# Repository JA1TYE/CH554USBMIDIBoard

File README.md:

# CH554 USB-MIDI Host Board

This board is designed to use [WCH's 8-bit MCU CH554](http://wch-ic.com/products/CH554.html) as a USB-MIDI Host.

Firmware for this board is available on [CH554USBMIDIHost](https://github.com/JA1TYE/CH554USBMIDIHost).

## How to use
CH554's UART0(TX:P3.1/RX:P3.0) are used as MIDI 1.0 I/F. 
CH554's UART1(TX:P1.7/RX:P1.6) are used for debugging.

This board have MIDI 1.0 compatible TX circuit(some resistors to consist current loop) but circuit for RX(i.e. optoisolator) is not contained. If you use MIDI1.0 RX, you should add optoisolator and so on.

You can use USB-A port and DEBUG UART (UART1) port to write firmware to CH554.
You need to power on with pressing SW1 to enter bootloader mode.

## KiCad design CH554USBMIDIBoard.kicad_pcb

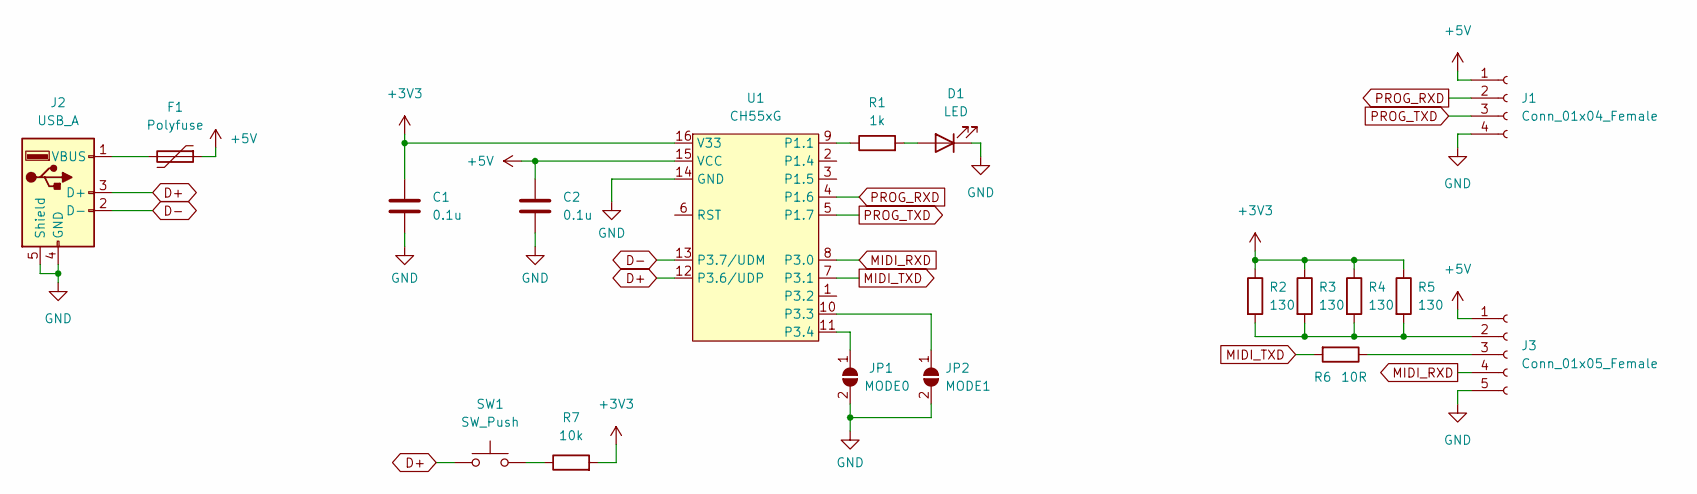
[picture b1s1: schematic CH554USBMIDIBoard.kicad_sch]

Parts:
C1, C2: 0.1u; C_0402_1005Metric
D1: LED; LED_0603_1608Metric
F1: Polyfuse; Fuse_1812_4532Metric
J1: Conn_01x04_Female; PinHeader_1x04_P2.54mm_Vertical
J2: USB_A; USB_A_Molex_67643_Horizontal
J3: Conn_01x05_Female; PinHeader_1x05_P2.54mm_Vertical
JP1: MODE0; SolderJumper-2_P1.3mm_Open_TrianglePad1.0x1.5mm
JP2: MODE1; SolderJumper-2_P1.3mm_Open_TrianglePad1.0x1.5mm
R1: 1k; R_0402_1005Metric
R2, R3, R4, R5: 130; R_0805_2012Metric
R6: 10R; R_0603_1608Metric
R7: 10k; R_0402_1005Metric
SW1: SW_Push; SW_Push_SPST_NO_Alps_SKRK
U1: CH55xG; SO-16_3.9x9.9mm_P1.27mm

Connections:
+3V3: C1.1, R2.1, R3.1, R4.1, R5.1, R7.2, U1.16 (V33)
+5V: C2.1, F1.1, J1.1, J3.1, U1.15 (VCC)
D+: J2.3 (D+), SW1.1, U1.12 (P3.6/UDP)
D-: J2.2 (D-), U1.13 (P3.7/UDM)
GND: C1.2, C2.2, D1.1 (K), J1.4, J2.4 (GND), J2.5 (Shield), J3.5, JP1.2 (B), JP2.2 (B), U1.14 (GND)
MIDI_RXD: J3.4, U1.8 (P3.0)
MIDI_TXD: R6.2, U1.7 (P3.1)
unnamed: D1.2 (A), R1.2
unnamed: F1.2, J2.1 (VBUS)
unnamed: J3.2, R2.2, R3.2, R4.2, R5.2
unnamed: J3.3, R6.1
unnamed: JP1.1 (A), U1.11 (P3.4)
unnamed: JP2.1 (A), U1.10 (P3.3)
unnamed: R1.1, U1.9 (P1.1)
unnamed: R7.1, SW1.2
PROG_RXD: J1.2, U1.4 (P1.6)
PROG_TXD: J1.3, U1.5 (P1.7)

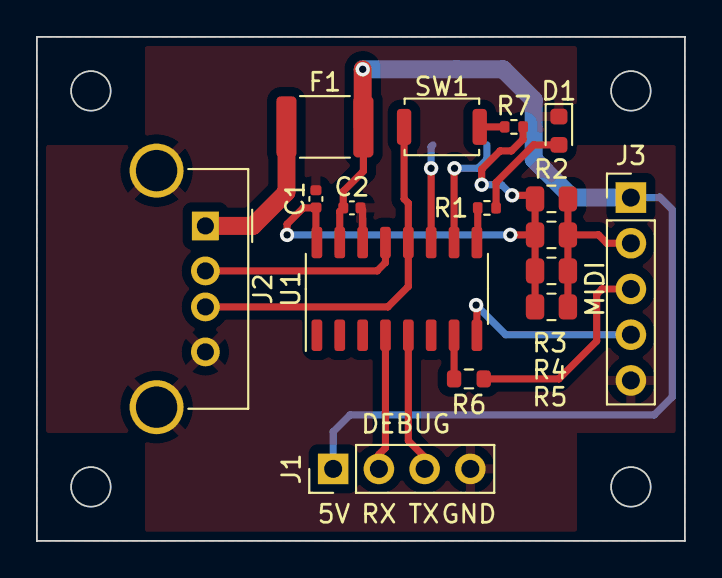
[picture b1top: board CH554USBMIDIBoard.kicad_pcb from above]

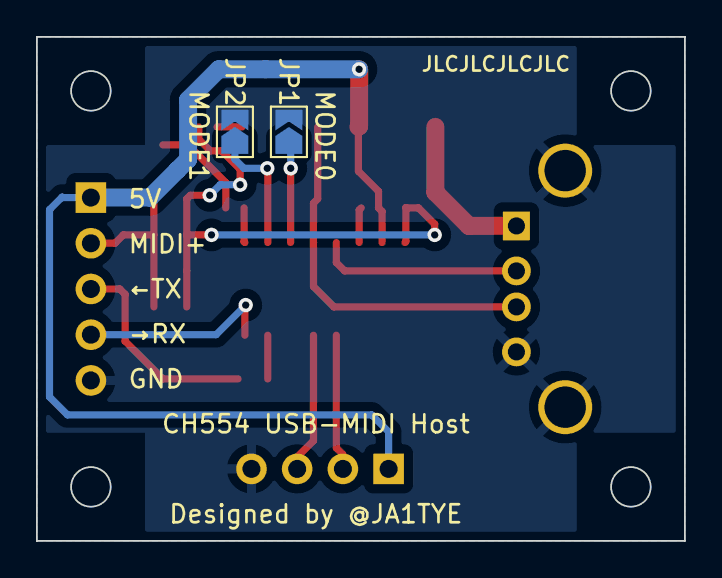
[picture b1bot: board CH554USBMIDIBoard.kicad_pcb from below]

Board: 2 copper layers, 36.0 x 28.0 mm, 18 parts (2 on the bottom side), 17 nets.

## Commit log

2023-01-27 1st commit
